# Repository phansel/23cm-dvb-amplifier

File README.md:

# 23cm DVB amplifier

This amplifier was designed in early 2019 for use as a telemetry/DVB radio for the University of Colorado COBRA/SRL rocket avionics project.

- ~ 4 watts (36 dBm) power output
- ~ 45 dB gain
- 1249 MHz center frequency

Note: editing this project requires at least KiCAD 5.99.

Copyright Paul Hansel (KC1GPW), 2019

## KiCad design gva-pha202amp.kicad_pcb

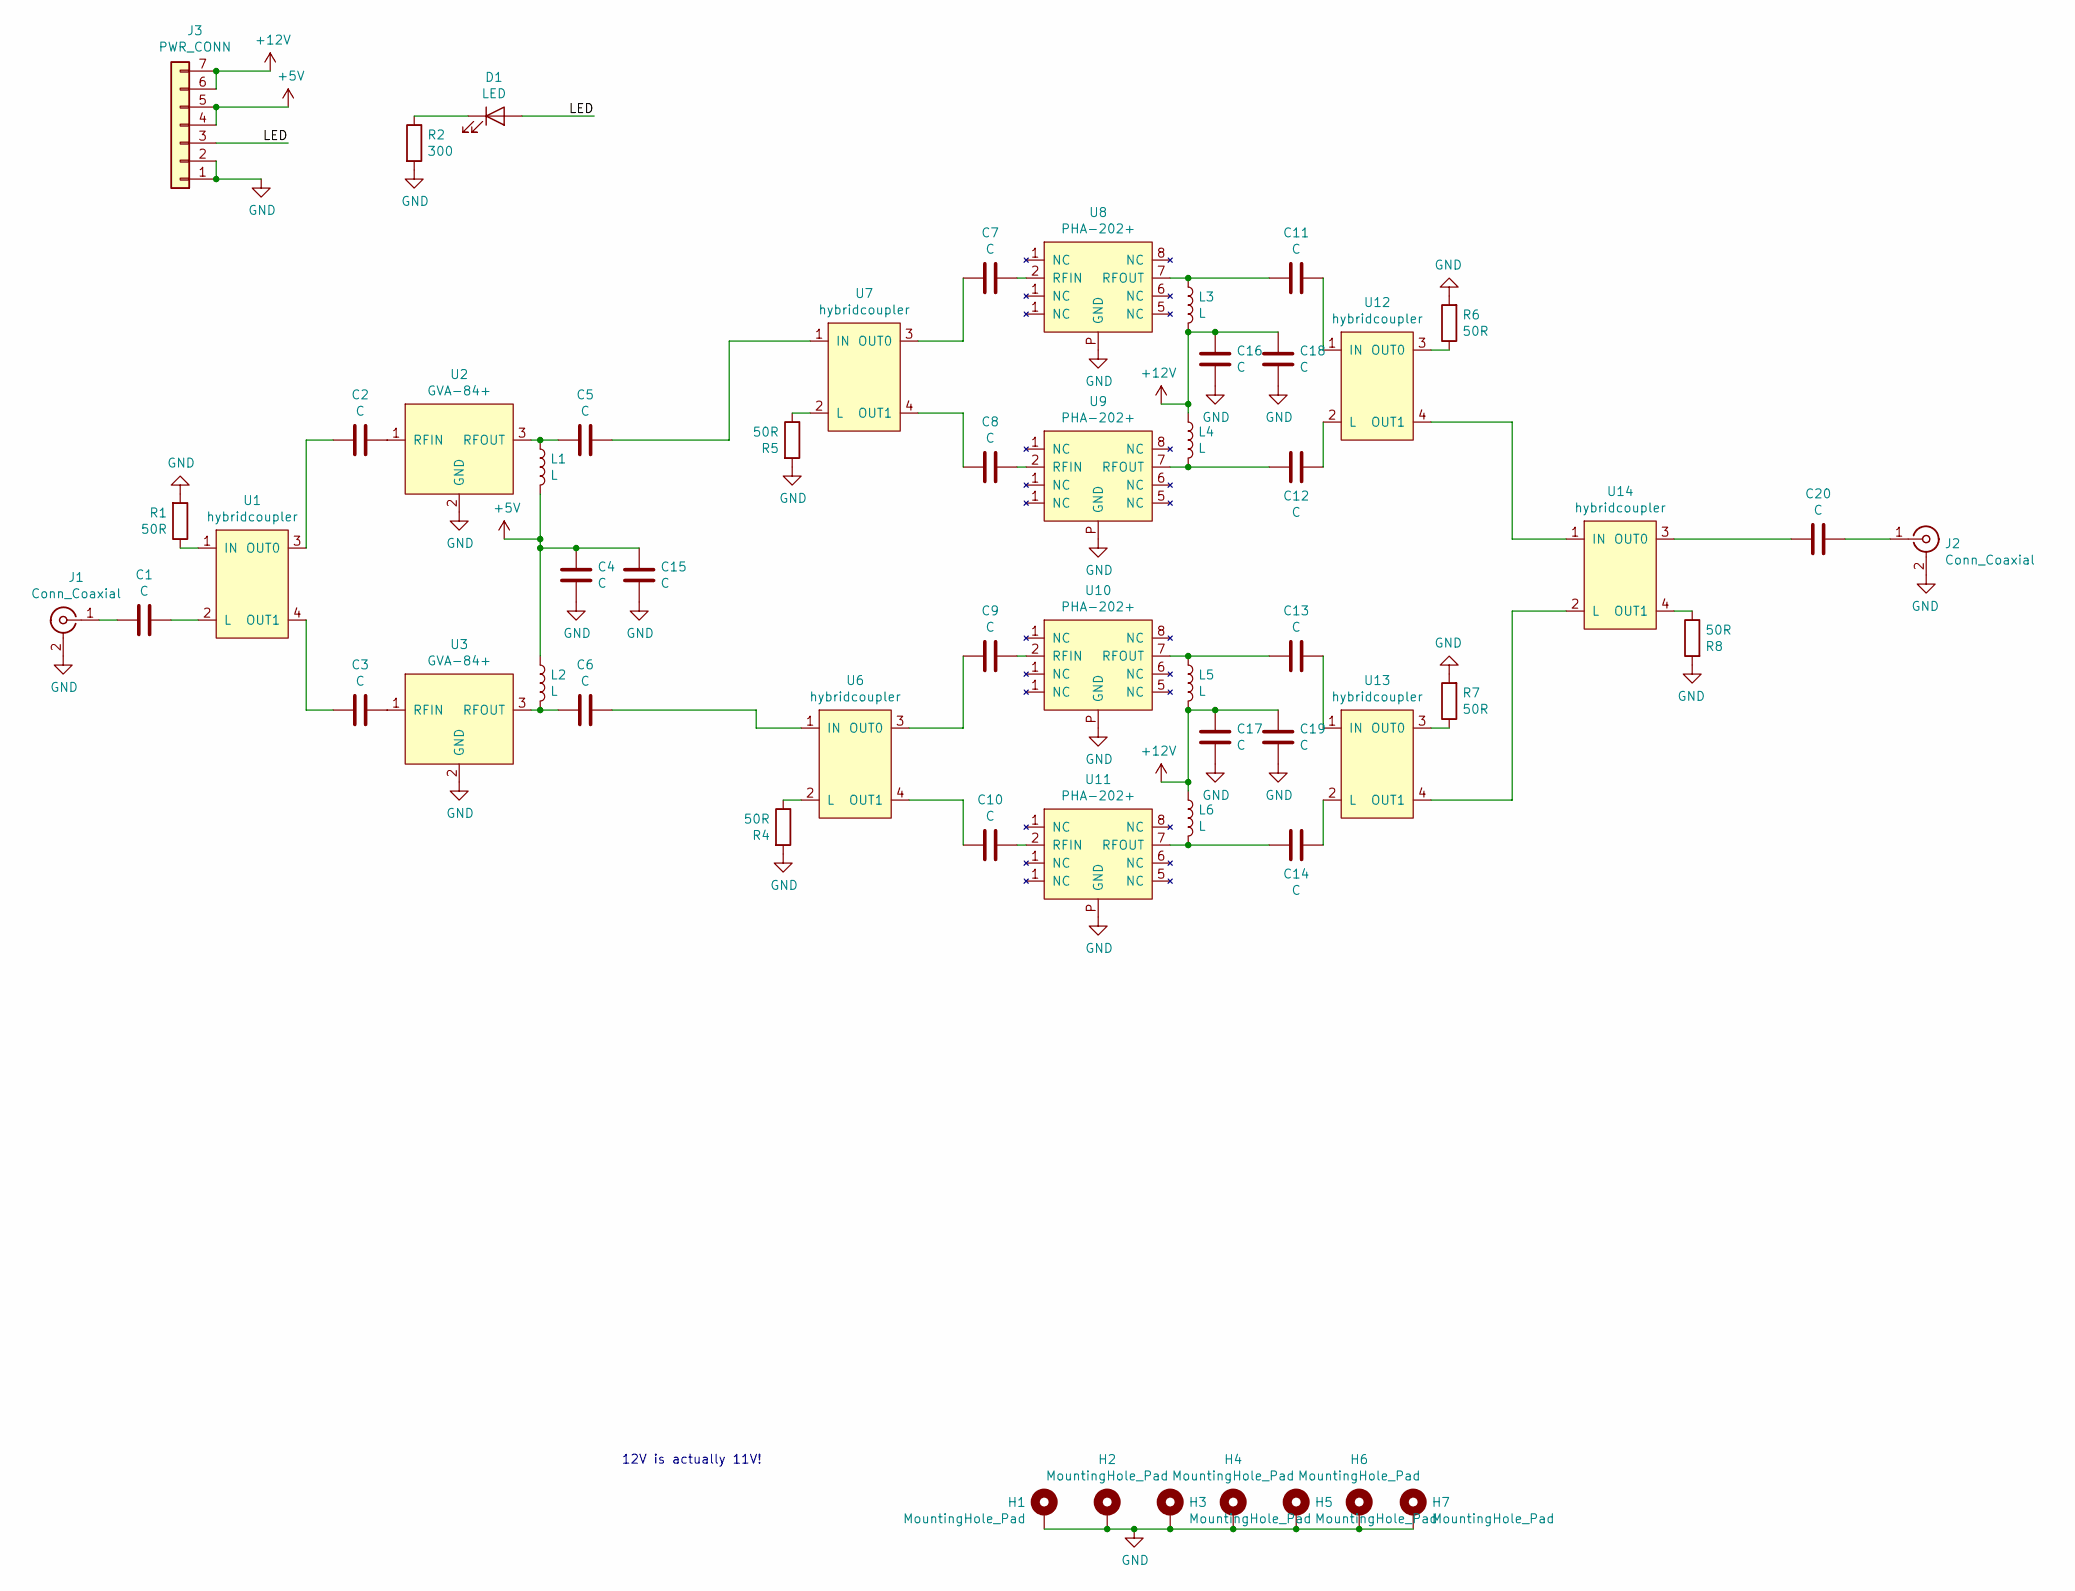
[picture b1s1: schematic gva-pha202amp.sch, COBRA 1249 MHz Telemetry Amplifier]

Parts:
C1, C20: C; C_0805_2012Metric
C2, C3, C4, C5, C6, C7, C8, C9, C10, C11, C12, C13, C14, C15, C16, C17, C18, C19: C; C_0603_1608Metric_Pad1.05x0.95mm_HandSolder
D1: LED; LED_0603_1608Metric
H1, H2, H3, H4, H5, H6, H7: MountingHole_Pad; MountingHole_2.2mm_M2_Pad_Via
J1, J2: Conn_Coaxial; SMA_Amphenol_132289_EdgeMount
J3: PWR_CONN; PinHeader_1x07_P2.54mm_Horizontal
L1, L2: L; C_0603_1608Metric_Pad1.05x0.95mm_HandSolder
L3, L4, L5, L6: L; C_0805_2012Metric_Pad1.15x1.40mm_HandSolder
R1, R4, R5: 50R; C_0603_1608Metric_Pad1.05x0.95mm_HandSolder
R2: 300; R_0603_1608Metric
R6, R7, R8: 50R; C_1206_3216Metric_Pad1.42x1.75mm_HandSolder
U1, U6, U7, U12, U13, U14: hybridcoupler; hybrid-branchline-coupler-1249
U2, U3: GVA-84+; SOT-89-3
U8, U9, U10, U11: PHA-202+; DL1636

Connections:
+5V: C4.2, C15.2, J3.4, J3.5, L1.2, L2.1
+12V: C16.2, C17.2, C18.2, C19.2, J3.6, J3.7, L3.2, L4.1, L5.2, L6.1
/LED: D1.2 (A), J3.3
GND: C4.1, C15.1, C16.1, C17.1, C18.1, C19.1, H1.1, H2.1, H3.1, H4.1, H5.1, H6.1, H7.1, J1.2 (Ext), J2.2 (Ext), J3.1, J3.2, R1.2, R2.2, R4.2, R5.2, R6.2, R7.2, R8.2, U2.2 (GND), U3.2 (GND), U8.P (GND), U9.P (GND), U10.P (GND), U11.P (GND)
unnamed: C1.1, U1.2 (L)
unnamed: C1.2, J1.1 (In)
unnamed: C2.1, U2.1 (RFIN)
unnamed: C2.2, U1.3 (OUT0)
unnamed: C3.1, U3.1 (RFIN)
unnamed: C3.2, U1.4 (OUT1)
unnamed: C5.1, U7.1 (IN)
unnamed: C5.2, L1.1, U2.3 (RFOUT)
unnamed: C6.1, U6.1 (IN)
unnamed: C6.2, L2.2, U3.3 (RFOUT)
unnamed: C7.1, U8.2 (RFIN)
unnamed: C7.2, U7.3 (OUT0)
unnamed: C8.1, U9.2 (RFIN)
unnamed: C8.2, U7.4 (OUT1)
unnamed: C9.1, U10.2 (RFIN)
unnamed: C9.2, U6.3 (OUT0)
unnamed: C10.1, U11.2 (RFIN)
unnamed: C10.2, U6.4 (OUT1)
unnamed: C11.1, U12.1 (IN)
unnamed: C11.2, L3.1, U8.7 (RFOUT)
unnamed: C12.1, U12.2 (L)
unnamed: C12.2, L4.2, U9.7 (RFOUT)
unnamed: C13.1, U13.1 (IN)
unnamed: C13.2, L5.1, U10.7 (RFOUT)
unnamed: C14.1, U13.2 (L)
unnamed: C14.2, L6.2, U11.7 (RFOUT)
unnamed: C20.1, J2.1 (In)
unnamed: C20.2, U14.3 (OUT0)
unnamed: D1.1 (K), R2.1
unnamed: R1.1, U1.1 (IN)
unnamed: R4.1, U6.2 (L)
unnamed: R5.1, U7.2 (L)
unnamed: R6.1, U12.3 (OUT0)
unnamed: R7.1, U13.3 (OUT0)
unnamed: R8.1, U14.4 (OUT1)
unnamed: U12.4 (OUT1), U14.1 (IN)
unnamed: U13.4 (OUT1), U14.2 (L)

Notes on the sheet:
12V is actually 11V!

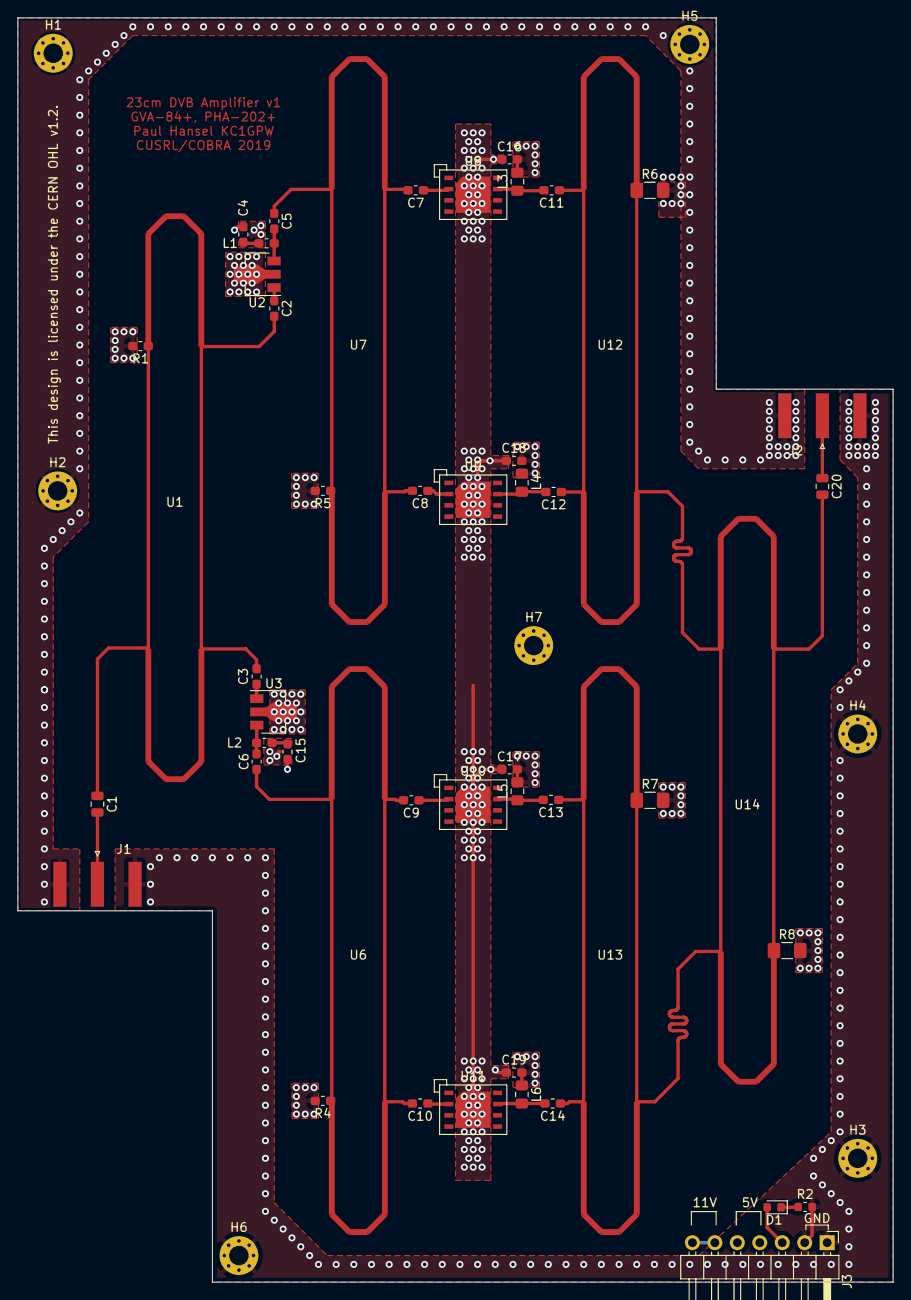
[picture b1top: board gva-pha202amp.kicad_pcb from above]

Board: 4 copper layers, 99.0 x 143.0 mm, 56 parts (0 on the bottom side), 41 nets.

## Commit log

2019-11-20 Added hw design files
2019-11-20 update license
2019-11-20 add image
2019-11-20 revisionism

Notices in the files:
gva-pha202amp.kicad_pcb:
This design is licensed under the CERN OHL v1.2.
gva-pha202amp.sch:
Copyright KC1GPW 2018
